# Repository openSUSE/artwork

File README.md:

# Artwork Repository
This is the repository of the openSUSE [artwork team](https://en.opensuse.org/openSUSE:Artwork_team).
While a version control system such as git may seem daunting, it is by far the
best option for collaborative authoring. GitHub is also relatively easy to use.

You can also read this guide in:

* [Español](README_es.md)

## License
All content in is licensed under [CC-BY-SA 3.0](https://creativecommons.org/licenses/by-sa/3.0/) unless
otherwise stated.

## Repository Structure

```
artwork/
├── logos/                  Brand logos (official, distros, events, teams, buttons)
├── promotional/            Marketing materials (banners, posters, flyers, social media)
├── events/                 Event materials (celebrations, quizzes, stickers)
├── presentations/          LibreOffice presentation templates
├── media/                  Video and image assets
├── hardware/               Hardware-related artwork (SBC graphics)
├── palettes/               Color palettes (GIMP .gpl files)
├── merchdesigns/           Merchandise designs
├── table-cloth/            Booth table cloth designs
├── proposed-for-deletion/  Items under review for removal
├── keep-and-organize/      Items to be kept (pending decision)
├── README.md               This file
├── README_es.md            Spanish translation
├── LICENSE.md              CC-BY-SA 3.0 license
└── .gitignore              Git ignore rules
```

## Contribute
### Initial setup
If you would like to modify or add material to our repository, you need to do
the following things first:

 1. register an account on GitHub, if you don't already have one
 2. install git (as root or use sudo, zypper install git), if you don't have it
    already
 3. See the GitHub help to set up your account and get an SSH key in there.
 4. ask admin@opensuse.org to add your user account to the team on github,
    which will give you write access to the repo.
 5. run the following commands in your ordinary user shell:
     1. git config --global user.email "my.email@address" (obviously with your
        real email address ;))
     2. git config --global user.name "John Doe" (again, with your real name)
 6. pick some directory where you'll want the files to reside, e.g. ~/Documents
    and go there in your shell, e.g. cd ~/Documents
 7. retrieve the repository with the following command as user: git clone
    git@github.com:openSUSE/artwork.git (which will create a subdirectory
    "artwork")

### Workflow
#### Getting the latest changes
In order to pull the latest changes that have been stored in the repository,
use the following command:

```shell
git pull
```

That will download the latest version of everything that is in the repository
on github, and store it on your disk.

Of course, that command needs to be ran from a shell while being in your local
artwork directory (e.g. ~/Documents/artwork)

#### Adding new files or directories
When you create a new file or directory, you have to tell git that you would
like to add it to the repository first, using the following command:

```shell
git add filename
```

(where you replace filename with the actual name of the file or directory you
want to add).

Note that adding a file does not upload it to the repository yet, it merely
instructs git that you want to put it under version control.

#### Committing changes
When you change files and you would like to store their state in the repository
(e.g. when you think it's good enough to be used by others), use the following
command:

```shell
git commit -m "some comment about the change I just made" filename
```

Please use meaningful comments (what's after -m) as that will help everyone to
keep track of the changes that were made. Also, make sure to put the comment
into quotes (between "") or the shell will interpret it as several parameters
for the git command, which it isn't.

You can also commit changes of several files at once, which is the preferred
approach when the changes do apply to several files (e.g. you just changed the
color palette on a dozen Inkscape files): that way, your changes will show up
as one "action" in the history of the repository.

To do so, just pass several filenames to the git commit command, like this:

```shell
git commit -m "changed palette to the right colors" filename1 filename2
filename3
```

You can also commit all the changes to all the files in your local copy of the
repository, by using the -a switch, like this:

```shell
git commit -m "changed palette to Bento colors" -a
```

#### Pushing changes
When you commit changes, git will only store them in your local repository on
your hard disk, and not to the artwork repository on github, which means that
no one else will be able to see your changes.

git works that way because you may choose to make changes locally, on your hard
disk, and keep track of those changes to be able to revert to a previous
version, without necessarily pushing those changes to all the other people who
work on the repository just yet.

Once you want to share your changes with everyone else, you must "push" those
changes to the repository, with the following command:

```shell
git push
```

Note that the very first time you will do a git push, you will have to use this
command: git push origin master

From then on, you will only need to use git push

Furthermore, when you want to push your changes to github, it is possible
that someone else already pushed other changes there. git will tell you see
when that happened, and you will just need to make a git pull before the git
push

Note Dolphin, KDE's file manager, has git support. The actions described above
can be done quite easily from there. Configure Dolphin and under Services you
can enable Git support. It will then automatically detect git folders and let
you add files you changed, make commits and push and pull changes.

#### Status
With the command git status, you can see whether you have files on your hard
disk that have changes (or new files, or deleted files) that have not been
committed yet.

```shell
git status
```

would output something like this:

```shell
# On branch master
# Changed but not updated:
#   (use "git add <file>..." to update what will be committed)
#   (use "git checkout -- <file>..." to discard changes in working directory)
#
#       modified:   git-mini-howto.txt
#
no changes added to commit (use "git add" and/or "git commit -a")
```
The output above means that the file git-mini-howto.txt is locally modified:
you have made changes to that file, but those changes are not committed (yet).

#### Removing files
If you want to delete a file from the repository, use git rm instead of
removing it as you would normally do (using rm filename or your favourite file
browser), like this:

```shell
git rm filename
```

Removing a file is just yet another change for git and, hence, to commit the
change: git commit -m "removed that file, it's obsolete now" filename (or the
other commit commands as explained above, such as git commit -a -m "...")

To push that change to github, for everyone:

```shell
git push
```

#### Renaming or moving files or directories
When you want to rename a file or directory, or move it elsewhere, do not use
the regular command-line or file manager options to do so. If you do that, git
will consider the renamed/moved file to be a new one and hence will lose the
history of changes.

The proper way of doing so is by using git mv, like this:

```shell
git mv old_filename new_filename
```

As usual, you will need to commit and push for that change to be visible for
everyone.

#### History
One of the most obvious advantages of version control systems such as git is
the ability to see the history of a file, which is a log of the modifications
that have been made, with the commit messages (see the -m option for git
commit), when changes were made and by whom.

To see the history of a file, use the following command:

```shell
git log filename
```

That will display something like this:

```shell
commit bbcf4e3a848d65fc28d1fb6d20d0ce7add040a33
Author: Pascal Bleser <pascal.bleser@opensuse.org>
Date:   Tue Feb 15 23:46:11 2011 +0100

    add LICENSE
```

There is only one change on the file above, but it shows

* whom made the change: Pascal Bleser
* when that change was made: Tue Feb 15
* what was changed (the commit message): "add LICENSE"

You can also see the all the changes, of the whole repository (and not just of
a single file), by using

```shell
git log
```

(without passing a file name)

Please note that git log commands automatically put the output into a pager
(normally that is /usr/bin/less), which gives you the ability to navigate the
output (with expected keys, such as arrow up, arrow down, page up, page down,
...). To leave the pager and return to the shell, simply press the key "q"
(mnemonics: "q" as in "quit").

git log has quite a few more options, which you can read about by typing git
log --help (also opens in the pager, press "q" to quit.)

### TODO

* document how to retrieve previous revisions of a file (git checkout)
* document how to reset your working environment to the state of the
  repository, to remove all your local changes (git reset --hard)
* mention graphical user interfaces (gitk, qgit, ...)
* link to other howtos, cheat sheets, etc, such as http://cheat.errtheblog.com/s/git

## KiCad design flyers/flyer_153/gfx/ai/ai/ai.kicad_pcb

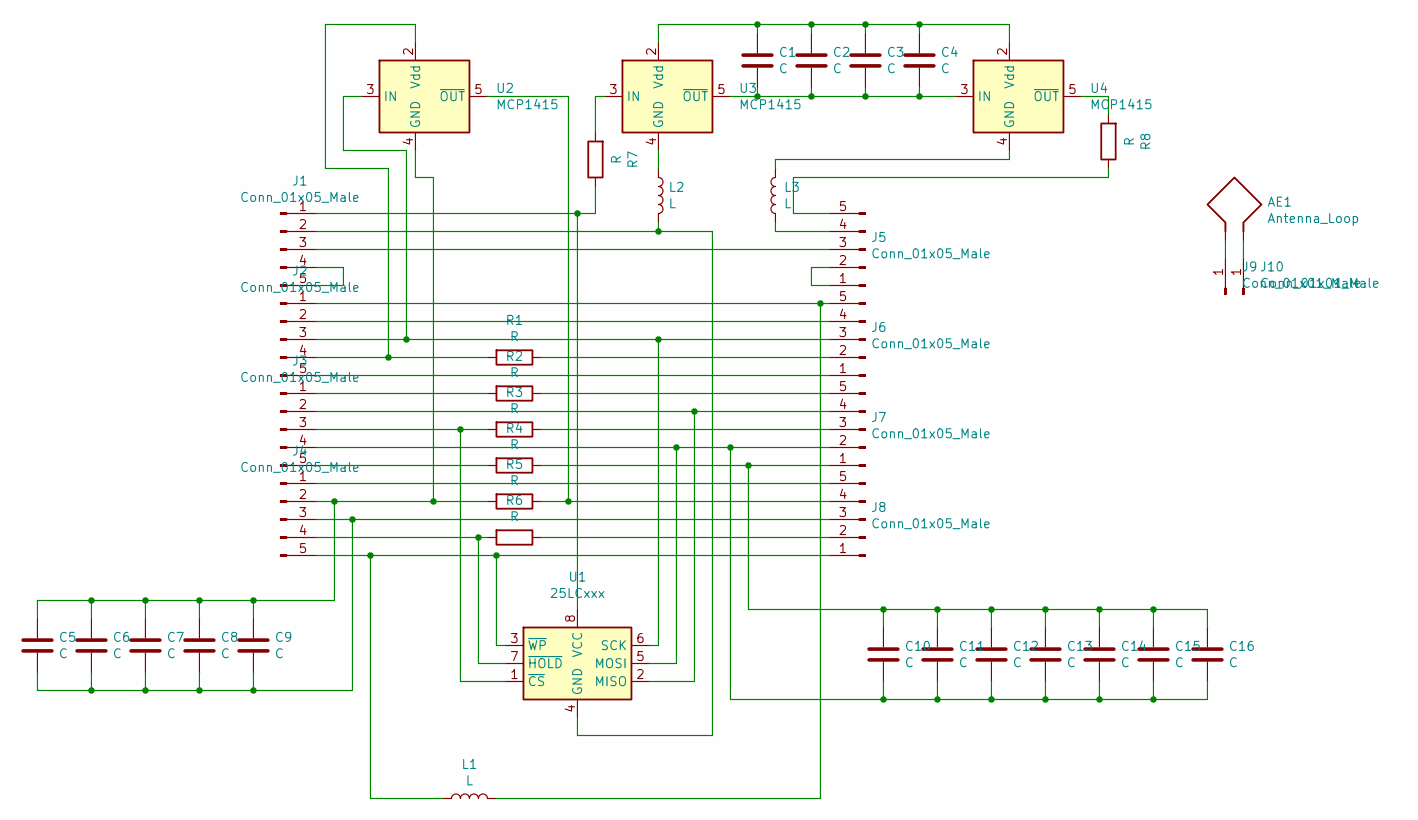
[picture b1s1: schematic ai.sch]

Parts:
AE1: Antenna_Loop
C1, C2, C3, C4, C14, C15, C16: C; C_0603_1608Metric
C5, C6, C7, C8, C9, C10, C11, C12, C13: C; CP_Elec_4x3
J1, J2, J3, J4, J5, J6, J7, J8: Conn_01x05_Male; PinHeader_1x05_P1.27mm_Vertical
J9, J10: Conn_01x01_Male; PinHeader_1x01_P2.54mm_Vertical
L1: L; L_6.3x6.3_H3
L2, L3: L; L_Wuerth_MAPI-4020
R1, R2, R3, R4, R5, R6, R7, R8: R; R_0805_2012Metric
U1: 25LCxxx; SOIC-8_3.9x4.9mm_P1.27mm
U2, U3, U4: MCP1415; SOT-23-5

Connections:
unnamed: AE1.1, J9.1
unnamed: AE1.2, J10.1
unnamed: C1.1, C2.1, C3.1, C4.1, U3.2 (Vdd), U4.2 (Vdd)
unnamed: C1.2, C2.2, C3.2, C4.2, U3.5 (~OUT), U4.3 (IN)
unnamed: C5.1, C6.1, C7.1, C8.1, C9.1, J4.2, R5.2, U2.4 (GND)
unnamed: C5.2, C6.2, C7.2, C8.2, C9.2, J4.3, J8.3
unnamed: C10.1, C11.1, C12.1, C13.1, C14.1, C15.1, C16.1, J7.1, R4.1
unnamed: C10.2, C11.2, C12.2, C13.2, C14.2, C15.2, C16.2, J3.4, J7.2, U1.5 (MOSI)
unnamed: J1.1, R7.1, U1.8 (VCC)
unnamed: J1.2, L2.2, U1.4 (GND)
unnamed: J1.3, J5.3
unnamed: J1.4, J1.5
unnamed: J2.1, J6.5, L1.2
unnamed: J2.2, J6.4
unnamed: J2.3, J6.3, U1.6 (SCK), U2.3 (IN)
unnamed: J2.4, R1.2, U2.2 (Vdd)
unnamed: J2.5, J6.1
unnamed: J3.1, R2.2
unnamed: J3.2, J7.4, U1.2 (MISO)
unnamed: J3.3, R3.2, U1.1 (~CS)
unnamed: J3.5, R4.2
unnamed: J4.1, J8.5
unnamed: J4.4, R6.2, U1.7 (~HOLD)
unnamed: J4.5, J8.1, L1.1, U1.3 (~WP)
unnamed: J5.1, J5.2
unnamed: J5.4, L3.1
unnamed: J5.5, R8.1
unnamed: J6.2, R1.1
unnamed: J7.3, R3.1
unnamed: J7.5, R2.1
unnamed: J8.2, R6.1
unnamed: J8.4, R5.1, U2.5 (~OUT)
unnamed: L2.1, U3.4 (GND)
unnamed: L3.2, U4.4 (GND)
unnamed: R7.2, U3.3 (IN)
unnamed: R8.2, U4.5 (~OUT)

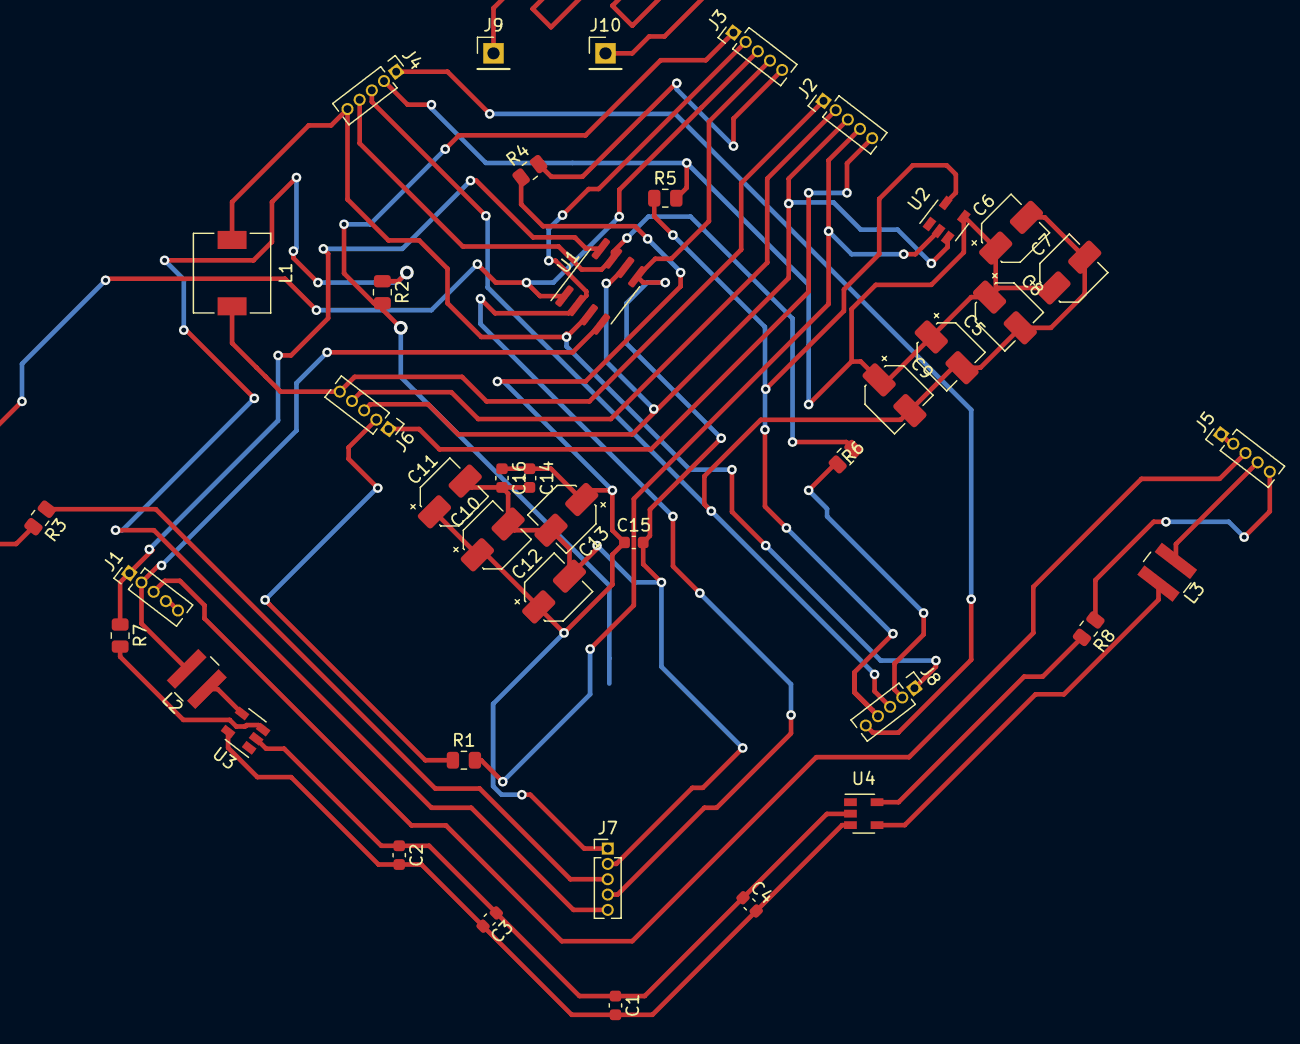
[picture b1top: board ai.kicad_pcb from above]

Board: 2 copper layers, 41 parts (0 on the bottom side), 34 nets.

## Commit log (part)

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2013-07-31 new file: Invitation Letter/Invitation Letterhead oSC13.svg modified: oSC13 Gazette/News_Paper_oSC13_04-Color.pdf modified: oSC13 Gazette/News_Paper_oSC13_04-Color.png
2013-07-31 deleted: News_Paper_oSC13_04-Color.pdf
2013-08-09 Summit Website mockups
2013-08-23 Minor fix to Evergreen logo
2013-09-12 updating Marketing material for 13.1
2013-09-18 add 120x90 13.1 banner
2013-09-18 updated G+ banners for 13.1 release
2013-09-21 Summit Marketing Materials
2013-09-25 Changes to CD Jacket for 13.1
2013-10-02 Added line "Sunday INSTALLFEST" for attendees to know what the plan is for the sunday gathering.
2013-10-04 New cameleon logo
2013-10-07 Add the 'release is coming' 13.1 artwork
2013-10-10 Updated summit flyers and Geeko hunt stickers
2013-10-13 Updated geeko money design
2013-10-17 add texture to release is coming
2013-10-20 add banner and background source files
2013-10-21 improved the we believe less test poster 4x3 for slides
2013-10-25 - arrange Geeko Hunt stickers in one document for printing
2013-10-25 - add money document for easy printing
2013-10-26 Keep Calm variations
2013-11-08 update logo
2013-11-11 add tumbleweed svg and openSUSE 13.1 presentation
2013-11-16 added an sticker for 13_1
2013-11-21 fix 13.1 presentation - invert OBS image
2013-12-06 remove the 'special edition' string
2013-12-14 4th anditosan logo proposal based on Trello proposals by Carlos Ribeiro
2013-12-16 new file: Osc14_logo_lucy.svg deleted: ../Chameleon_Logo_Test.tif deleted: ../DSC_4690.JPG deleted: ../Logo.psd deleted: ../Logo_Proposal2.png deleted: ../Logo_Proposal2.svg deleted: ../Logo_Proposal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
2013-12-17 add gerneric version of cd sleeve too
2013-12-25 new file: Geeko_Xmas_01.png new file: Geeko_Xmas_01.svg new file: Geeko_Xmas_02.png new file: Geeko_Xmas_02.svg
2013-12-26 new file: FelizAnoNovo_openSUSE2014.svg new file: oS_New_Year2014-02.svg new file: oS_New_Year2014.svg
2013-12-29 oSC14 Conference T-shirts
2014-01-03 new file: ../../../../miscellaneous/oS_New_Year2014-03.png new file: ../../../../miscellaneous/oS_New_Year2014-03.svg
2014-01-08 new file: Cheat Cube/11.2/openSUSE_112_Cheat_CubeA3_01.png new file: Cheat Cube/11.2/openSUSE_112_Cheat_CubeA3_01.svg new file: Cheat Cube/11.3/openSUSE_general_Cheat_Cube-v01.png new file: Cheat Cub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
2014-01-15 modified: GeekoMoney_04.pdf modified: GeekoMoney_04.png modified: GeekoMoney_04.svg
2014-01-16 modified: Folding Tux oSC14_01.pdf modified: Folding Tux oSC14_01.png modified: Folding Tux oSC14_01.svg modified: Folding Tux oSC14_02.pdf modified: Folding Tux oSC14_02.png modified: Folding Tux oS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
2014-01-18 modified: Folding Cube oSC14.svg new file: Folding Cube oSC14_02-Preview.png new file: Folding Cube oSC14_02.pdf new file: Folding Cube oSC14_02.png new file: Folding Cube oSC14_02.svg
2014-01-18 new file: Poster oSC14-preview.png new file: Poster oSC14.pdf new file: Poster oSC14.png new file: Poster oSC14.svg
2014-01-18 Anditosan Edition
2014-01-18 Anditosan poster version
2014-01-19 deleted: ../../2013-oS-Conference/GeekoMoney/IMG_20130621_183903_610.jpg new file: GeekoMoney_05.pdf new file: GeekoMoney_05.png new file: GeekoMoney_05.svg deleted: ../Posters/Poster oSC14-preview.p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
2014-01-19 new file: Poster oSC14-FinalVersion-CMYK.pdf new file: Poster oSC14-FinalVersion.pdf new file: Poster oSC14-FinalVersion.png new file: Poster oSC14-FinalVersion.svg deleted: ../Proposal_05 - Poster o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
2014-01-19 new file: GeekoMoney_Final.pdf new file: GeekoMoney_Final.png new file: GeekoMoney_Final.svg new file: GeekoMoney_Final_PREVIEW_LOWRESOLUTION.png deleted: ../GeekoMoney_05.pdf deleted: ../GeekoMoney_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
2014-01-20 new file: ../../PromoCube/Final/PromoCube oSC14_Final-CMYK.pdf new file: ../../PromoCube/Final/PromoCube oSC14_Final.pdf new file: ../../PromoCube/Final/PromoCube oSC14_Final.svg
2014-01-20 modified: Final/PromoCube oSC14_Final-CMYK.pdf
2014-01-20 new file: Folding Tux oSC14_Final.pdf new file: Folding Tux oSC14_Final.png new file: Folding Tux oSC14_Final.svg modified: ../Folding Tux oSC14_01.svg
2014-01-20 modified: PromoCube oSC14_Final.png modified: PromoCube oSC14_Final.svg
2014-01-20 modified: Poster oSC14-FinalVersion.svg
2014-01-21 new file: GeekoMoney_Final_a4-NOT_ROTATED.pdf new file: GeekoMoney_Final_a4-NOT_ROTATED.png new file: GeekoMoney_Final_a4-NOT_ROTATED.svg
2014-01-21 Logo with large font to embed into Websites
2014-01-28 deleted: GeekoMoney_Final_PREVIEW_LOWRESOLUTION.png deleted: GeekoMoney_Final_a4-NOT_ROTATED.pdf deleted: GeekoMoney_Final_a4-NOT_ROTATED.png deleted: GeekoMoney_Final_a4-NOT_ROTATED.svg deleted: Gee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
2014-02-01 modified: SponsorBrochure/Sponsorship Brochure Back oSC14.svg deleted: SponsorBrochure/Sponsorship Brochure Front oSC14.svg
2014-02-12 Brochure work in progress
2014-02-12 More editing
2014-02-15 Edited light brochure version
2014-02-24 Last minute changes
2014-03-06 Banners and logo fixes for conference materials
2014-04-10 sponsored by A3 posters for the openSUSE Conference 2014
2014-06-16 playing with Marcus proposals
2014-07-04 Added Wallpaper for openSUSE 13.2
2014-11-07 openSUSE 13.2 promoDVD face and sleeve design
2014-11-20 Adding directories for 2015 openSUSE conference
2014-11-26 13.2 inspired master slides
2014-11-26 another one based on colours of Adny logo
2014-12-09 another lizard's logo proposal
2014-12-15 OSC sticker with grey
    Stickers for FOSDEM for OSC15
2014-12-15 psd file for OSC15 sticker
    psd file for stickers for FOSDEM for OSC15
2015-01-20 pin for Kostas and cleanup logo image
2015-04-02 Added Slide Template from https://news.opensuse.org/2015/04/01/saving-time-on-your-osc15-presentation/
2015-08-05 presentation slides about openSUSE 13.2 for OpenRheinRuhr 2014 in German
2015-10-11 New translation of the openSUSE Brochure for Hungarian
2015-11-11 adding openSUSE 42.1 (Leap) Box image
2016-01-11 Add official logos
2016-06-09 Add Tumbleweed & Leap logos
2016-07-14 Correct monochrome logo with Registered trademark logo
2016-08-23 New binding brochure
2016-09-12 Portus sticker
2016-09-12 obs sticker
2017-01-20 add banners
2017-01-24 Get the year right
2017-04-15 Remove .DS_Store, remove spurious urlencode dirs
    - Transfert files from urlencode dirs to normal places
    Marketing%20Materials
    Marketing%2520Materials
    - Remove any still existant .DS_Store, add them to .gitignore
2018-03-27 Create oSC Logo
2018-04-27 Fix template notes
2018-04-28 Add pirate sticker based on design of green pirate flag
2018-05-08 New update with updated alex image
2018-05-11 Change logos by permission of board
2018-05-17 Add initial artwork for teams
2018-05-17 Supporting graphic for booths at conferences
    Supporting graphic can be used for roll-up banners and at events that require a background images.
2018-05-20 Remove irrelevant logos
2018-05-21 Improve logos and add Heroes one
2018-05-21 Add License text
2018-06-18 Logo that can be used for a new project
    These can be used as a logo for a new openSUSE project
2018-07-25 OBS Skull
2018-07-25 alex white
2018-10-08 add a Spanish translation for README file
2018-10-10 Will place popup banners in here
2018-11-06 Add files via upload
    YaST logo used for sticker making for OpenFest 2018 event
2018-12-04 Advertisement
2019-01-22 New OBS Sticker for 2019 eps
2019-02-05 black and white
2019-03-16 Redo the structure
2019-04-03 Add sticker designed by IvoErMejo
2019-05-08 change the logo from the old format
2019-05-08 replace two-colour version logo
2019-05-08 change two-color logo to correct logo
2020-02-06 finish translation
2020-02-07 fix align, fix OBS name writting, add missing spaces in OSC commands
2020-02-08 fix missing space in mount cmd
2020-02-10 WIP: recreate english version
2020-06-08 Release-Flyer 15.2 - initial commit
    - changed "System Requirements" to some Kernel info
    - added discord icon to "Connect"
2020-06-09 Kernel-info added; Discord added; Printing-info
2020-07-01 Container image for Twitter banner
2020-08-20 Initial recognition example with openSUSE button
    * This is just an example, I'd really appreciate more personalized
    graphics.
    * Done per ovationcore's example which will be used for SUSE Employees
2020-08-21 Use medal graphics vinzv as a banner
    * Use Banner made out of https://progress.opensuse.org/issues/63823
    * Center the banner to aligh with text
    * Use monochromatic button under the signature
2020-08-21 Use openSUSE font 'Source Sans Pro'
2020-08-31 Use different aspect ratio for banner, dark border and cellspacing
2020-08-31 fix the local testing link
2020-09-02 Add script to generate and send recognition emails
2020-10-05 template for openSUSE LibreOffice Conference
2020-10-12 Delete oSLO 2020 slide template.odp
    Need a 16:9 view. 4:3 won't work look good.
2021-02-12 put in teams
2021-04-21 Add files via upload
    - "You can download..." centered
    - "A bootable media..." -> "Bootable media..."
    - "A detailed..." -> "Detailed..."
    - updated URL
    - Matrix Channel corrected
2021-05-10 OpenSans, AI-Image and some formatting
    New version with OpenSans as the default font
    p1: Replaced Logo with Leap-Logo (borders are stillcut though)
    p2/3: replaced bitmap with vector graphics, reformatted the text
    p4:
    back/front: clipping of hexagons fixed
    TO DO
2021-05-16 4th draft
    p1: Updated AI-logo, changed title, shortened text and added geeko icon
    p4: Shortened text, added white icons, replaced image (and website)
    p5: Changed subject to »Start with openSUSE«, added text and icons
    p6: Deleted text about installation and aligned to p5 and p7
    p5, p6: Removed hexagons at bottom
    TO DO
2021-05-27 Goldmaster/May 27 all: spell-checking, added printable version front: Cover-image color-balanced + added shadow p1: ai-image color-balanced added printable version (*-print.pdf)
2021-05-27 emoved folding marks
2021-06-01 Add prototype distro logos
2021-07-01 Bump 15.2 recognition to 15.3
2021-09-20 Fix overlapping nodes
    Fixed 2 pairs of overlapping nodes that were located on the top left of the lower and upper case e's
2021-11-26 Create Sjenica1
    Authorized mit meine Account Sjenica1 github.com reufrujevic750@gmail.com
2022-03-30 Adjust kubic to feedback
2022-06-06 Create text
2022-06-06 Data of Flyer for Leap 15.4
2022-06-16 add png
2022-06-17 let's get wild
2022-07-29 colors to be discussed
2022-10-06 Simple video intro and endscreen
    * made in videobolt.net, video license attached
    * lkocman paid the fee and donates the art as it is to openSUSE project
2022-10-06 keep endscreen plain simple
2022-10-12 use optimized svg
2022-10-13 optipng -o7 for zypp-team.png
2023-02-06 Add footer about reloading images for all templates
2023-02-15 recognition: use comma as default delimiter
2023-03-22 openSUSE Conference Template
    Updated for oSC23
2023-03-29 Add openSUSE Booth quiz leaflets
2023-03-29 fix colors of headings
2023-06-09 Add initial banner for 15.5 recognitions
2023-09-28 Refreshed quizzes for LinuxDays 2023.
    * Fixes #73
2023-10-11 Use giga privileges also in En variant
2023-10-18 stickers update of Aeon
2023-10-19 use markdown for quiz readme
2024-01-09 Add Leap 16.0 annoucement banner
2024-01-11 Lighter version of Leap 16 banner by nektarije
2024-03-07 Add little gif for NZXT Kraken AIO pump.
    * can be seen here https://news.opensuse.org/wp-content/uploads/2024/03/leap156-beta-testing.jpg
2024-03-22 Move Quizzes into a separate directory
    * makes contributions more straightforward as people
    had hard time to look it up
2024-03-23 Add files via upload
    Logo ideas for openSUSECon 2024. I know yellow isn't part of the guidelines but it adds some brightness to it. If not, one of the two files uses all colors and tints from the guidelines. I also tried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
2024-05-28 Add initial logo for openSUSE cloud team
    Background image in te logo was designed by Freepik
2024-09-10 Update README.txt
    added main content to Graphics_Templates README file
2024-09-10 Add files via upload
    SELinux openSUSE announcement: se penguin petting chameleon
2024-09-10 Update se_penguin_chameleon.svg
    deleted incorrect file
2024-09-10 Update se_penguin_chameleon.svg
    deleting incorrect svg file
2024-09-20 SE Linux openSUSE shift
2024-10-15 Add updated linuxdays 2024 cz/en quiz
2025-02-24 adding logos
2025-05-13 Delete Graphics_Templates directory
    Deleting folder since it would be a duplicate with "Images for news.o.o and social media" folder, graphic contributions should go to the latter
2025-06-02 Add button-filled-colour style transparent logo
2025-06-26 upload logo for oSC25
2025-07-10 Pi Zero inspired sbc
2025-08-14 Add 20years white sticker which works nice on black T
2025-11-24 Added .png buttons and .pxo source file
